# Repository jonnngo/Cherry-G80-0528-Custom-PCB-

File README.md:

This is a very early work in progress, I aim to fix/improve upon this first iteration very soon. This project is supposed to be a custom PCB replacement for the Cherry G80-0528 powered by a much more modern microcontroller (STM32F411), QMK firmware, using usb-c. Made using KiCad.

Some fixes I have planned:
1. The matrix needs to use less microcontroller pins to make room for the LED indicators as well as the crystal oscillator circuit
2. There are two mounting columns that secure the PCB to the keyboard case, which I will need to add holes for
3. Either a daughterboard for the usb-c receptacle, or make sure the usb-c receptacle has proper spacing for a cable to be fixed

9/2/2026
I have completely redone the schematic and pcb. I squared the matrix making more room for the indicator LEDs, the matrix now takes 22 pins instead of 28. The traces for the columns and rows a little messier now because of this. The "forehead" is much smaller now, so there should be no problems with fixing a cable to the board and fitting in the original case.
1. Still need to add the 2 mounting holes
2. connect the +3.3V pins
3. connect ground pins to the ground planes

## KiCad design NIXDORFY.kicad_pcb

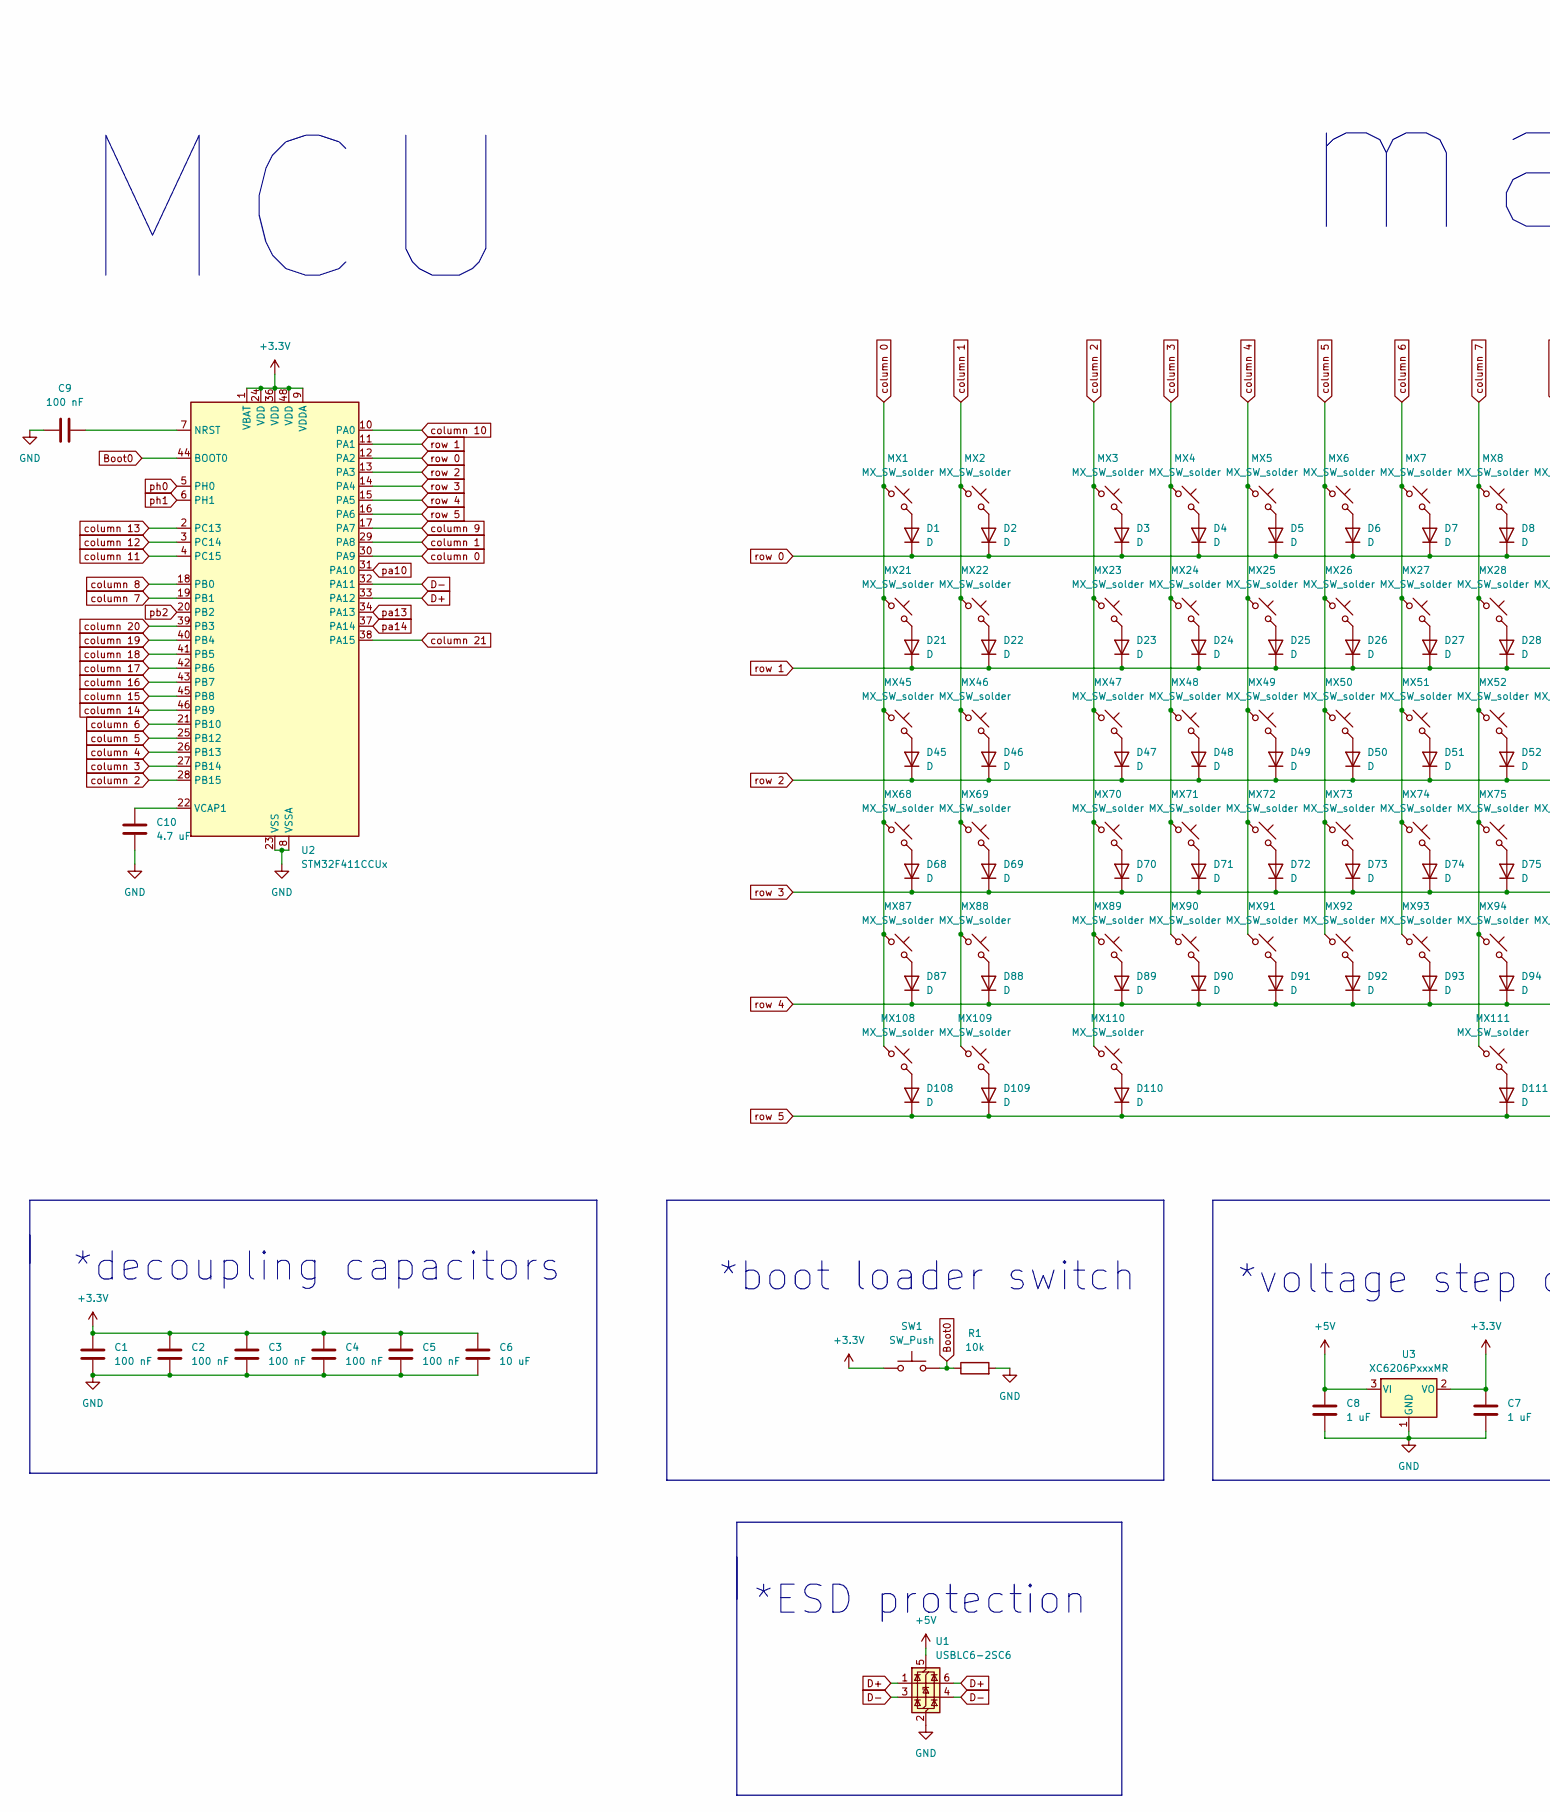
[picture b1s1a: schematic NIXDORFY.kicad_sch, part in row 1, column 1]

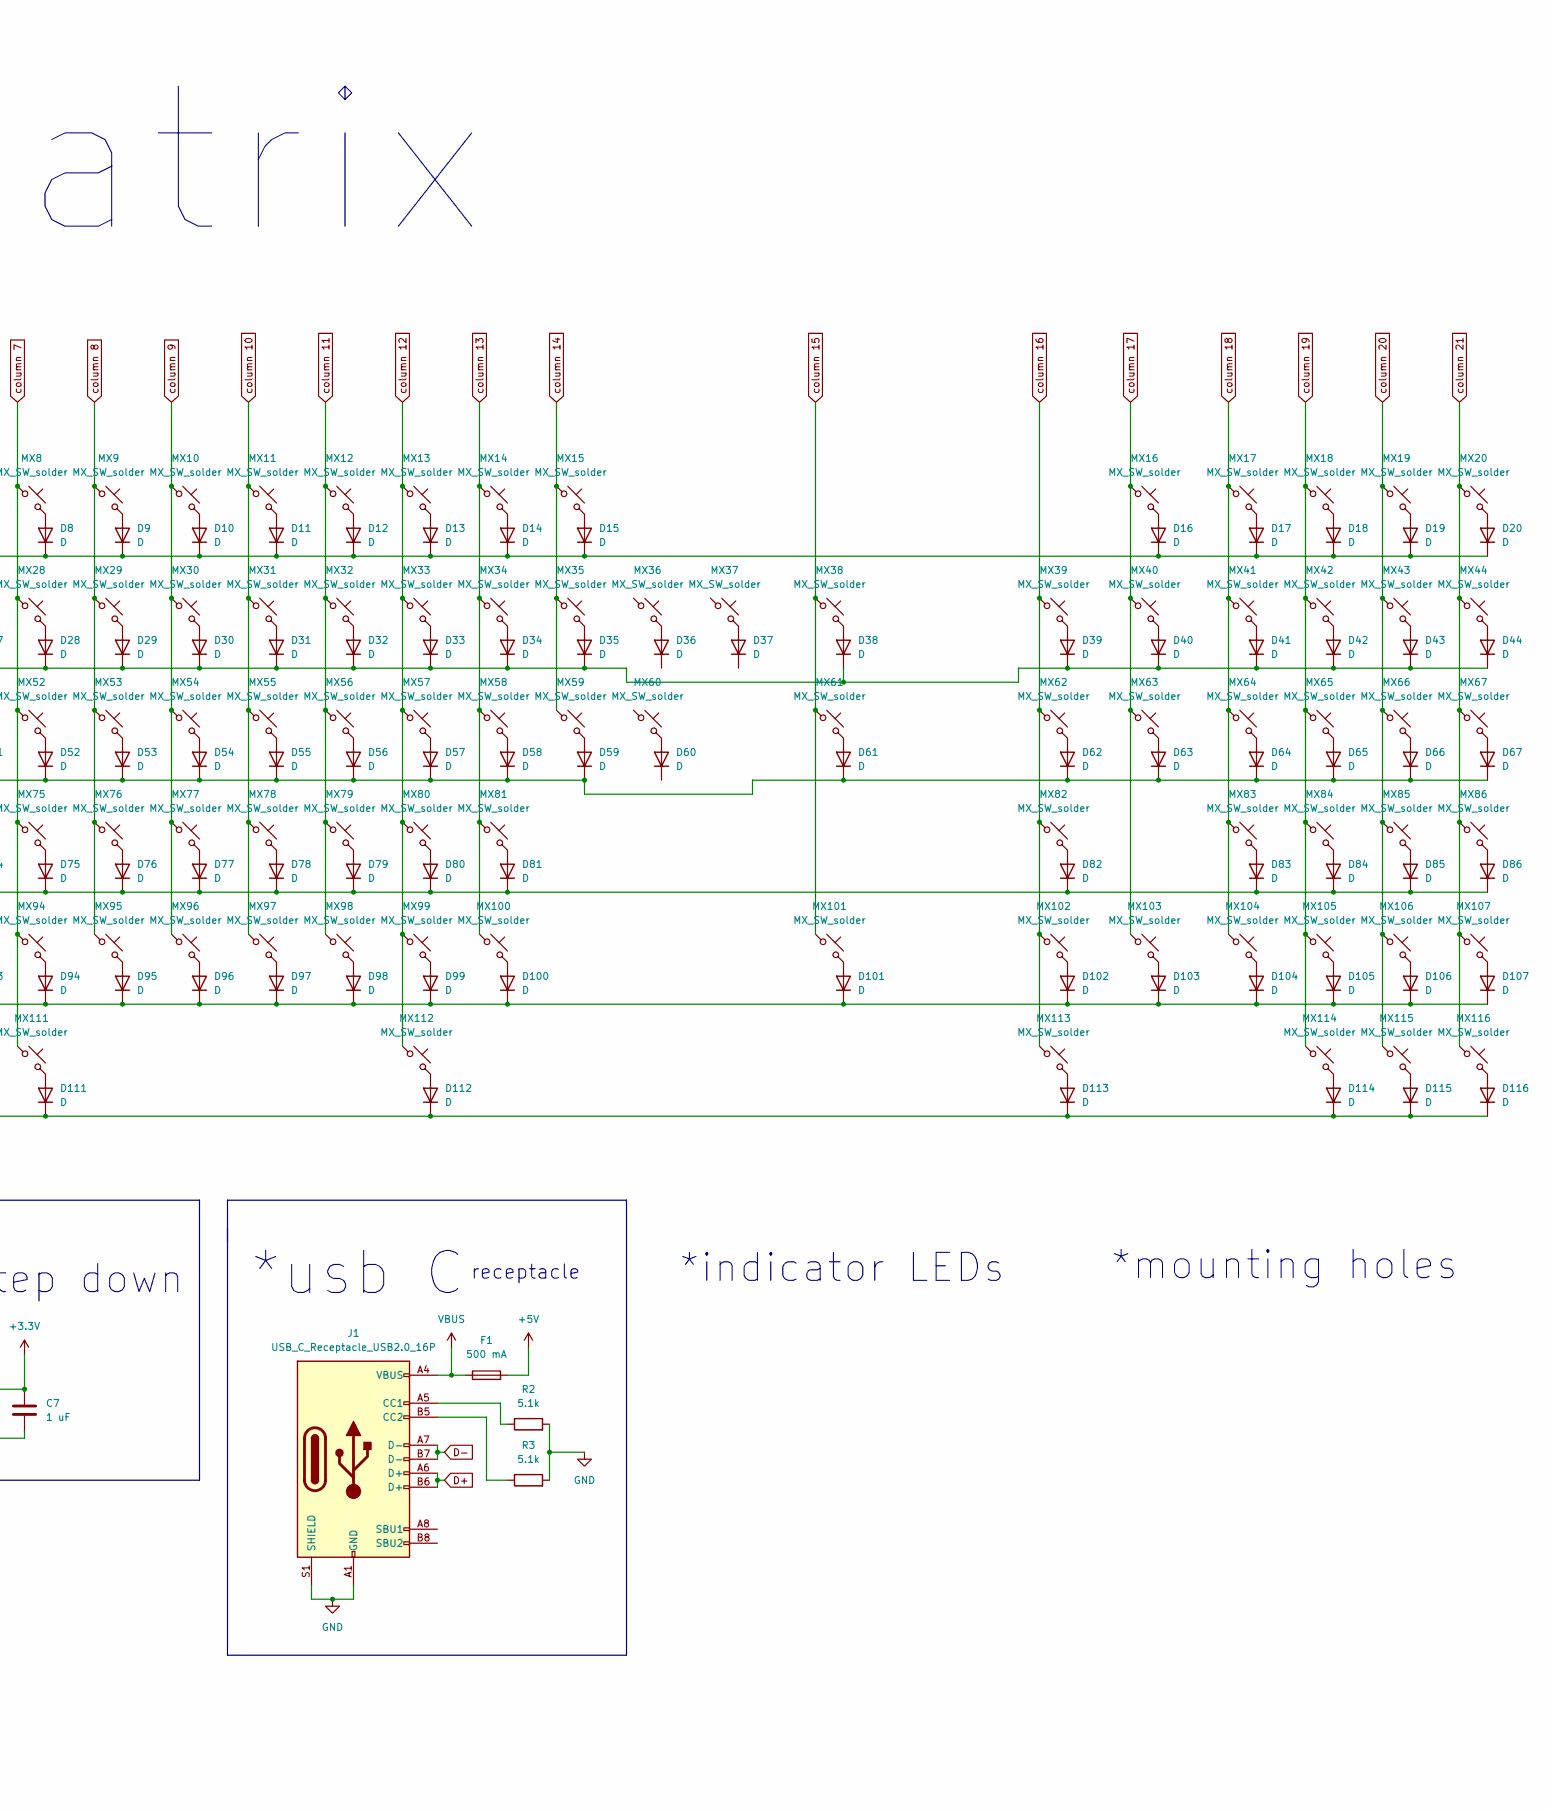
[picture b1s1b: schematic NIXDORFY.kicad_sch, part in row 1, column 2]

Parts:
C1, C2, C3, C4, C5, C9: 100 nF; C_0603_1608Metric
C6: 10 uF; C_0805_2012Metric
C7, C8: 1 uF; C_0603_1608Metric
C10: 4.7 uF; C_0603_1608Metric
D1, D2, D3, D4, D5, D6, D7, D8, D9, D10, D11, D12, D13, D14, D15, D16, D17, D18, D19, D20, D21, D22, D23, D24, D25, D26, D27, D28, D29, D30, D31, D32, D33, D34, D35, D36, D37, D38, D39, D40, D41, D42, D43, D44, D45, D46, D47, D48, D49, D50, D51, D52, D53, D54, D55, D56, D57, D58, D59, D60, D61, D62, D63, D64, D65, D66, D67, D68, D69, D70, D71, D72, D73, D74, D75, D76, D77, D78, D79, D80, D81, D82, D83, D84, D85, D86, D87, D88, D89, D90, D91, D92, D93, D94, D95, D96, D97, D98, D99, D100, D101, D102, D103, D104, D105, D106, D107, D108, D109, D110, D111, D112, D113, D114, D115, D116: D; D_SOD-123
F1: 500 mA; Fuse_1206_3216Metric
J1: USB_C_Receptacle_USB2.0_16P; USB_C_Receptacle_HRO_TYPE-C-31-M-12
MX1, MX2, MX3, MX4, MX5, MX6, MX7, MX8, MX9, MX10, MX11, MX12, MX13, MX14, MX15, MX16, MX17, MX18, MX19, MX20, MX21, MX22, MX23, MX24, MX25, MX26, MX27, MX28, MX29, MX30, MX31, MX32, MX33, MX34, MX35, MX36, MX37, MX38, MX39, MX40, MX41, MX42, MX43, MX44, MX45, MX46, MX47, MX48, MX49, MX50, MX51, MX52, MX53, MX54, MX55, MX56, MX57, MX58, MX59, MX60, MX61, MX62, MX63, MX64, MX65, MX66, MX67, MX68, MX69, MX70, MX71, MX72, MX73, MX74, MX75, MX76, MX77, MX78, MX79, MX80, MX81, MX82, MX83, MX84, MX85, MX86, MX87, MX88, MX89, MX90, MX91, MX92, MX93, MX94, MX95, MX96, MX97, MX98, MX99, MX100, MX101, MX102, MX103, MX104, MX105, MX106, MX107, MX108, MX109, MX110, MX111, MX112, MX113, MX114, MX115, MX116: MX_SW_solder; SW_MX_1u
R1: 10k; R_0603_1608Metric
R2, R3: 5.1k; R_0603_1608Metric
SW1: SW_Push; SW_SPST_FSMSM
U1: USBLC6-2SC6; SOT-23-6
U2: STM32F411CCUx; QFN-48-1EP_7x7mm_P0.5mm_EP5.6x5.6mm
U3: XC6206PxxxMR; SOT-23-3

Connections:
+3.3V: C1.1, C2.1, C3.1, C4.1, C5.1, C6.1, C7.1, SW1.1, U2.1 (VBAT), U2.9 (VDDA), U2.24 (VDD), U2.36 (VDD), U2.48 (VDD), U3.2 (VO)
+5V: C8.1, F1.2, U1.5 (VBUS), U3.3 (VI)
Boot0: R1.1, SW1.2, U2.44 (BOOT0)
D+: J1.A6 (D+), J1.B6 (D+), U1.1 (I/O1), U1.6 (I/O1), U2.33 (PA12)
D-: J1.A7 (D-), J1.B7 (D-), U1.3 (I/O2), U1.4 (I/O2), U2.32 (PA11)
GND: C1.2, C2.2, C3.2, C4.2, C5.2, C6.2, C7.2, C8.2, C9.1, C10.2, J1.A1 (GND), J1.A12 (GND), J1.B1 (GND), J1.B12 (GND), J1.S1 (SHIELD), R1.2, R2.2, R3.2, U1.2 (GND), U2.8 (VSSA), U2.23 (VSS), U2.35 (VSS), U2.47 (VSS), U2.49 (VSS), U3.1 (GND)
unnamed: D1.2 (A), MX1.2
unnamed: D2.2 (A), MX2.2
unnamed: D3.2 (A), MX3.2
unnamed: D4.2 (A), MX4.2
unnamed: D5.2 (A), MX5.2
unnamed: D6.2 (A), MX6.2
unnamed: D7.2 (A), MX7.2
unnamed: D8.2 (A), MX8.2
unnamed: D9.2 (A), MX9.2
unnamed: D10.2 (A), MX10.2
unnamed: D11.2 (A), MX11.2
unnamed: D12.2 (A), MX12.2
unnamed: D13.2 (A), MX13.2
unnamed: D14.2 (A), MX14.2
unnamed: D15.2 (A), MX15.2
unnamed: D16.2 (A), MX16.2
unnamed: D17.2 (A), MX17.2
unnamed: D18.2 (A), MX18.2
unnamed: D19.2 (A), MX19.2
unnamed: D20.2 (A), MX20.2
unnamed: D21.2 (A), MX21.2
unnamed: D22.2 (A), MX22.2
unnamed: D23.2 (A), MX23.2
unnamed: D24.2 (A), MX24.2
unnamed: D25.2 (A), MX25.2
unnamed: D26.2 (A), MX26.2
unnamed: D27.2 (A), MX27.2
unnamed: D28.2 (A), MX28.2
unnamed: D29.2 (A), MX29.2
unnamed: D30.2 (A), MX30.2
unnamed: D31.2 (A), MX31.2
unnamed: D32.2 (A), MX32.2
unnamed: D33.2 (A), MX33.2
unnamed: D34.2 (A), MX34.2
unnamed: D35.2 (A), MX35.2
unnamed: D36.2 (A), MX36.2
unnamed: D37.2 (A), MX37.2
unnamed: D38.2 (A), MX38.2
unnamed: D39.2 (A), MX39.2
unnamed: D40.2 (A), MX40.2
unnamed: D41.2 (A), MX41.2
unnamed: D42.2 (A), MX42.2
unnamed: D43.2 (A), MX43.2
unnamed: D44.2 (A), MX44.2
unnamed: D45.2 (A), MX45.2
unnamed: D46.2 (A), MX46.2
unnamed: D47.2 (A), MX47.2
unnamed: D48.2 (A), MX48.2
unnamed: D49.2 (A), MX49.2
unnamed: D50.2 (A), MX50.2
unnamed: D51.2 (A), MX51.2
unnamed: D52.2 (A), MX52.2
unnamed: D53.2 (A), MX53.2
unnamed: D54.2 (A), MX54.2
unnamed: D55.2 (A), MX55.2
unnamed: D56.2 (A), MX56.2
unnamed: D57.2 (A), MX57.2
unnamed: D58.2 (A), MX58.2
unnamed: D59.2 (A), MX59.2
unnamed: D60.2 (A), MX60.2
unnamed: D61.2 (A), MX61.2
unnamed: D62.2 (A), MX62.2
unnamed: D63.2 (A), MX63.2
unnamed: D64.2 (A), MX64.2
unnamed: D65.2 (A), MX65.2
unnamed: D66.2 (A), MX66.2
unnamed: D67.2 (A), MX67.2
unnamed: D68.2 (A), MX68.2
unnamed: D69.2 (A), MX69.2
unnamed: D70.2 (A), MX70.2
unnamed: D71.2 (A), MX71.2
unnamed: D72.2 (A), MX72.2
unnamed: D73.2 (A), MX73.2
unnamed: D74.2 (A), MX74.2
unnamed: D75.2 (A), MX75.2
unnamed: D76.2 (A), MX76.2
unnamed: D77.2 (A), MX77.2
unnamed: D78.2 (A), MX78.2
unnamed: D79.2 (A), MX79.2
unnamed: D80.2 (A), MX80.2
unnamed: D81.2 (A), MX81.2
unnamed: D82.2 (A), MX82.2
unnamed: D83.2 (A), MX83.2
unnamed: D84.2 (A), MX84.2
unnamed: D85.2 (A), MX85.2
unnamed: D86.2 (A), MX86.2
unnamed: D87.2 (A), MX87.2
unnamed: D88.2 (A), MX88.2
unnamed: D89.2 (A), MX89.2
unnamed: D90.2 (A), MX90.2
unnamed: D91.2 (A), MX91.2
unnamed: D92.2 (A), MX92.2
unnamed: D93.2 (A), MX93.2
unnamed: D94.2 (A), MX94.2
unnamed: D95.2 (A), MX95.2
unnamed: D96.2 (A), MX96.2
unnamed: D97.2 (A), MX97.2
unnamed: D98.2 (A), MX98.2
unnamed: D99.2 (A), MX99.2
unnamed: D100.2 (A), MX100.2
unnamed: D101.2 (A), MX101.2
unnamed: D102.2 (A), MX102.2
unnamed: D103.2 (A), MX103.2
unnamed: D104.2 (A), MX104.2
unnamed: D105.2 (A), MX105.2
unnamed: D106.2 (A), MX106.2
unnamed: D107.2 (A), MX107.2
unnamed: D108.2 (A), MX108.2
unnamed: D109.2 (A), MX109.2
unnamed: D110.2 (A), MX110.2
unnamed: D111.2 (A), MX111.2
unnamed: D112.2 (A), MX112.2
unnamed: D113.2 (A), MX113.2
unnamed: D114.2 (A), MX114.2
unnamed: D115.2 (A), MX115.2
unnamed: D116.2 (A), MX116.2
unnamed: J1.A5 (CC1), R2.1
unnamed: J1.B5 (CC2), R3.1
unnamed: C9.2, U2.7 (NRST)
unnamed: C10.1, U2.22 (VCAP1)
VBUS: F1.1, J1.A4 (VBUS), J1.A9 (VBUS), J1.B4 (VBUS), J1.B9 (VBUS)
column 0: MX1.1, MX21.1, MX45.1, MX68.1, MX87.1, MX108.1, U2.30 (PA9)
column 1: MX2.1, MX22.1, MX46.1, MX69.1, MX88.1, MX109.1, U2.29 (PA8)
column 2: MX3.1, MX23.1, MX47.1, MX70.1, MX89.1, MX110.1, U2.28 (PB15)
column 3: MX4.1, MX24.1, MX48.1, MX71.1, MX90.1, U2.27 (PB14)
column 4: MX5.1, MX25.1, MX49.1, MX72.1, MX91.1, U2.26 (PB13)
column 5: MX6.1, MX26.1, MX50.1, MX73.1, MX92.1, U2.25 (PB12)
column 6: MX7.1, MX27.1, MX51.1, MX74.1, MX93.1, U2.21 (PB10)
column 7: MX8.1, MX28.1, MX52.1, MX75.1, MX94.1, MX111.1, U2.19 (PB1)
column 8: MX9.1, MX29.1, MX53.1, MX76.1, MX95.1, U2.18 (PB0)
column 9: MX10.1, MX30.1, MX54.1, MX77.1, MX96.1, U2.17 (PA7)
column 10: MX11.1, MX31.1, MX55.1, MX78.1, MX97.1, U2.10 (PA0)
column 11: MX12.1, MX32.1, MX56.1, MX79.1, MX98.1, U2.4 (PC15)
column 12: MX13.1, MX33.1, MX57.1, MX80.1, MX99.1, MX112.1, U2.3 (PC14)
column 13: MX14.1, MX34.1, MX58.1, MX81.1, MX100.1, U2.2 (PC13)
column 14: MX15.1, MX35.1, MX59.1, MX60.1, U2.46 (PB9)
column 15: MX36.1, MX38.1, MX61.1, MX101.1, U2.45 (PB8)
column 16: MX37.1, MX39.1, MX62.1, MX82.1, MX102.1, MX113.1, U2.43 (PB7)
column 17: MX16.1, MX40.1, MX63.1, MX103.1, U2.42 (PB6)
column 18: MX17.1, MX41.1, MX64.1, MX83.1, MX104.1, U2.41 (PB5)
column 19: MX18.1, MX42.1, MX65.1, MX84.1, MX105.1, MX114.1, U2.40 (PB4)
column 20: MX19.1, MX43.1, MX66.1, MX85.1, MX106.1, MX115.1, U2.39 (PB3)
column 21: MX20.1, MX44.1, MX67.1, MX86.1, MX107.1, MX116.1, U2.38 (PA15)
pa10: U2.31 (PA10)
pa13: U2.34 (PA13)
pa14: U2.37 (PA14)
pb2: U2.20 (PB2)
ph0: U2.5 (PH0)
ph1: U2.6 (PH1)
row 0: D1.1 (K), D2.1 (K), D3.1 (K), D4.1 (K), D5.1 (K), D6.1 (K), D7.1 (K), D8.1 (K), D9.1 (K), D10.1 (K), D11.1 (K), D12.1 (K), D13.1 (K), D14.1 (K), D15.1 (K), D16.1 (K), D17.1 (K), D18.1 (K), D19.1 (K), D20.1 (K), D36.1 (K), D37.1 (K), U2.12 (PA2)
row 1: D21.1 (K), D22.1 (K), D23.1 (K), D24.1 (K), D25.1 (K), D26.1 (K), D27.1 (K), D28.1 (K), D29.1 (K), D30.1 (K), D31.1 (K), D32.1 (K), D33.1 (K), D34.1 (K), D35.1 (K), D38.1 (K), D39.1 (K), D40.1 (K), D41.1 (K), D42.1 (K), D43.1 (K), D44.1 (K), U2.11 (PA1)
row 2: D45.1 (K), D46.1 (K), D47.1 (K), D48.1 (K), D49.1 (K), D50.1 (K), D51.1 (K), D52.1 (K), D53.1 (K), D54.1 (K), D55.1 (K), D56.1 (K), D57.1 (K), D58.1 (K), D59.1 (K), D61.1 (K), D62.1 (K), D63.1 (K), D64.1 (K), D65.1 (K), D66.1 (K), D67.1 (K), U2.13 (PA3)
row 3: D60.1 (K), D68.1 (K), D69.1 (K), D70.1 (K), D71.1 (K), D72.1 (K), D73.1 (K), D74.1 (K), D75.1 (K), D76.1 (K), D77.1 (K), D78.1 (K), D79.1 (K), D80.1 (K), D81.1 (K), D82.1 (K), D83.1 (K), D84.1 (K), D85.1 (K), D86.1 (K), U2.14 (PA4)
row 4: D87.1 (K), D88.1 (K), D89.1 (K), D90.1 (K), D91.1 (K), D92.1 (K), D93.1 (K), D94.1 (K), D95.1 (K), D96.1 (K), D97.1 (K), D98.1 (K), D99.1 (K), D100.1 (K), D101.1 (K), D102.1 (K), D103.1 (K), D104.1 (K), D105.1 (K), D106.1 (K), D107.1 (K), U2.15 (PA5)
row 5: D108.1 (K), D109.1 (K), D110.1 (K), D111.1 (K), D112.1 (K), D113.1 (K), D114.1 (K), D115.1 (K), D116.1 (K), U2.16 (PA6)

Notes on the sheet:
*decoupling capacitors
matrix
*ESD protection
*voltage step down
*usb C
receptacle
*mounting holes
*boot loader switch
MCU
*indicator LEDs

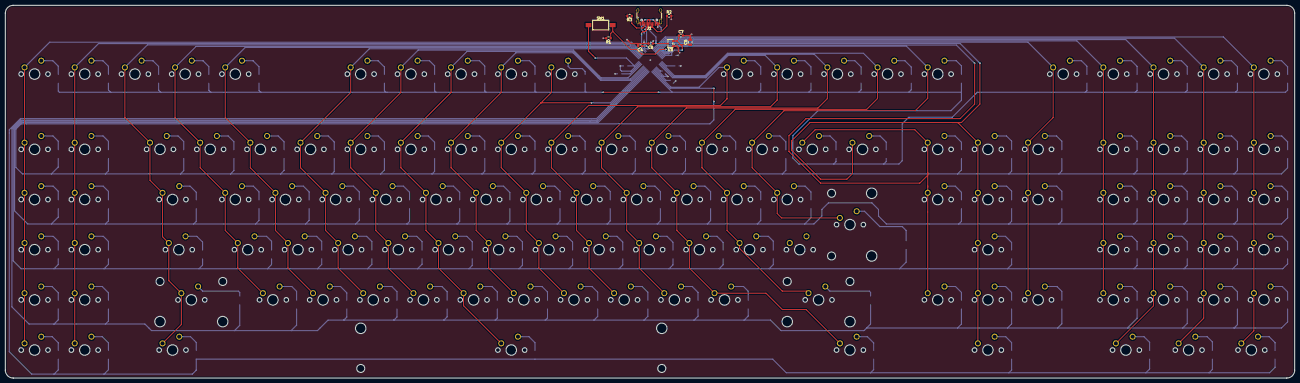
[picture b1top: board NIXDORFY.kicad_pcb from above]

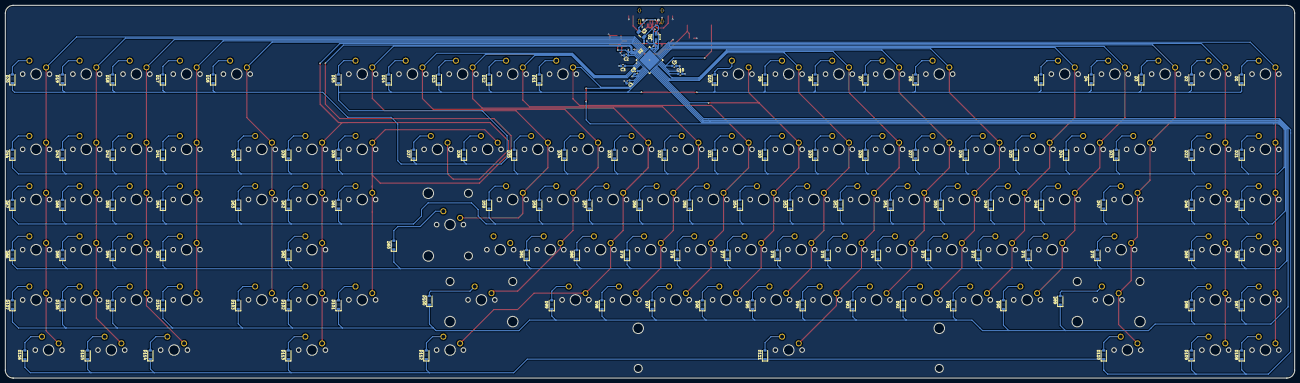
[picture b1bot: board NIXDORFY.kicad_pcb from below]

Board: 2 copper layers, 489.5 x 141.5 mm, 251 parts (125 on the bottom side), 155 nets.
